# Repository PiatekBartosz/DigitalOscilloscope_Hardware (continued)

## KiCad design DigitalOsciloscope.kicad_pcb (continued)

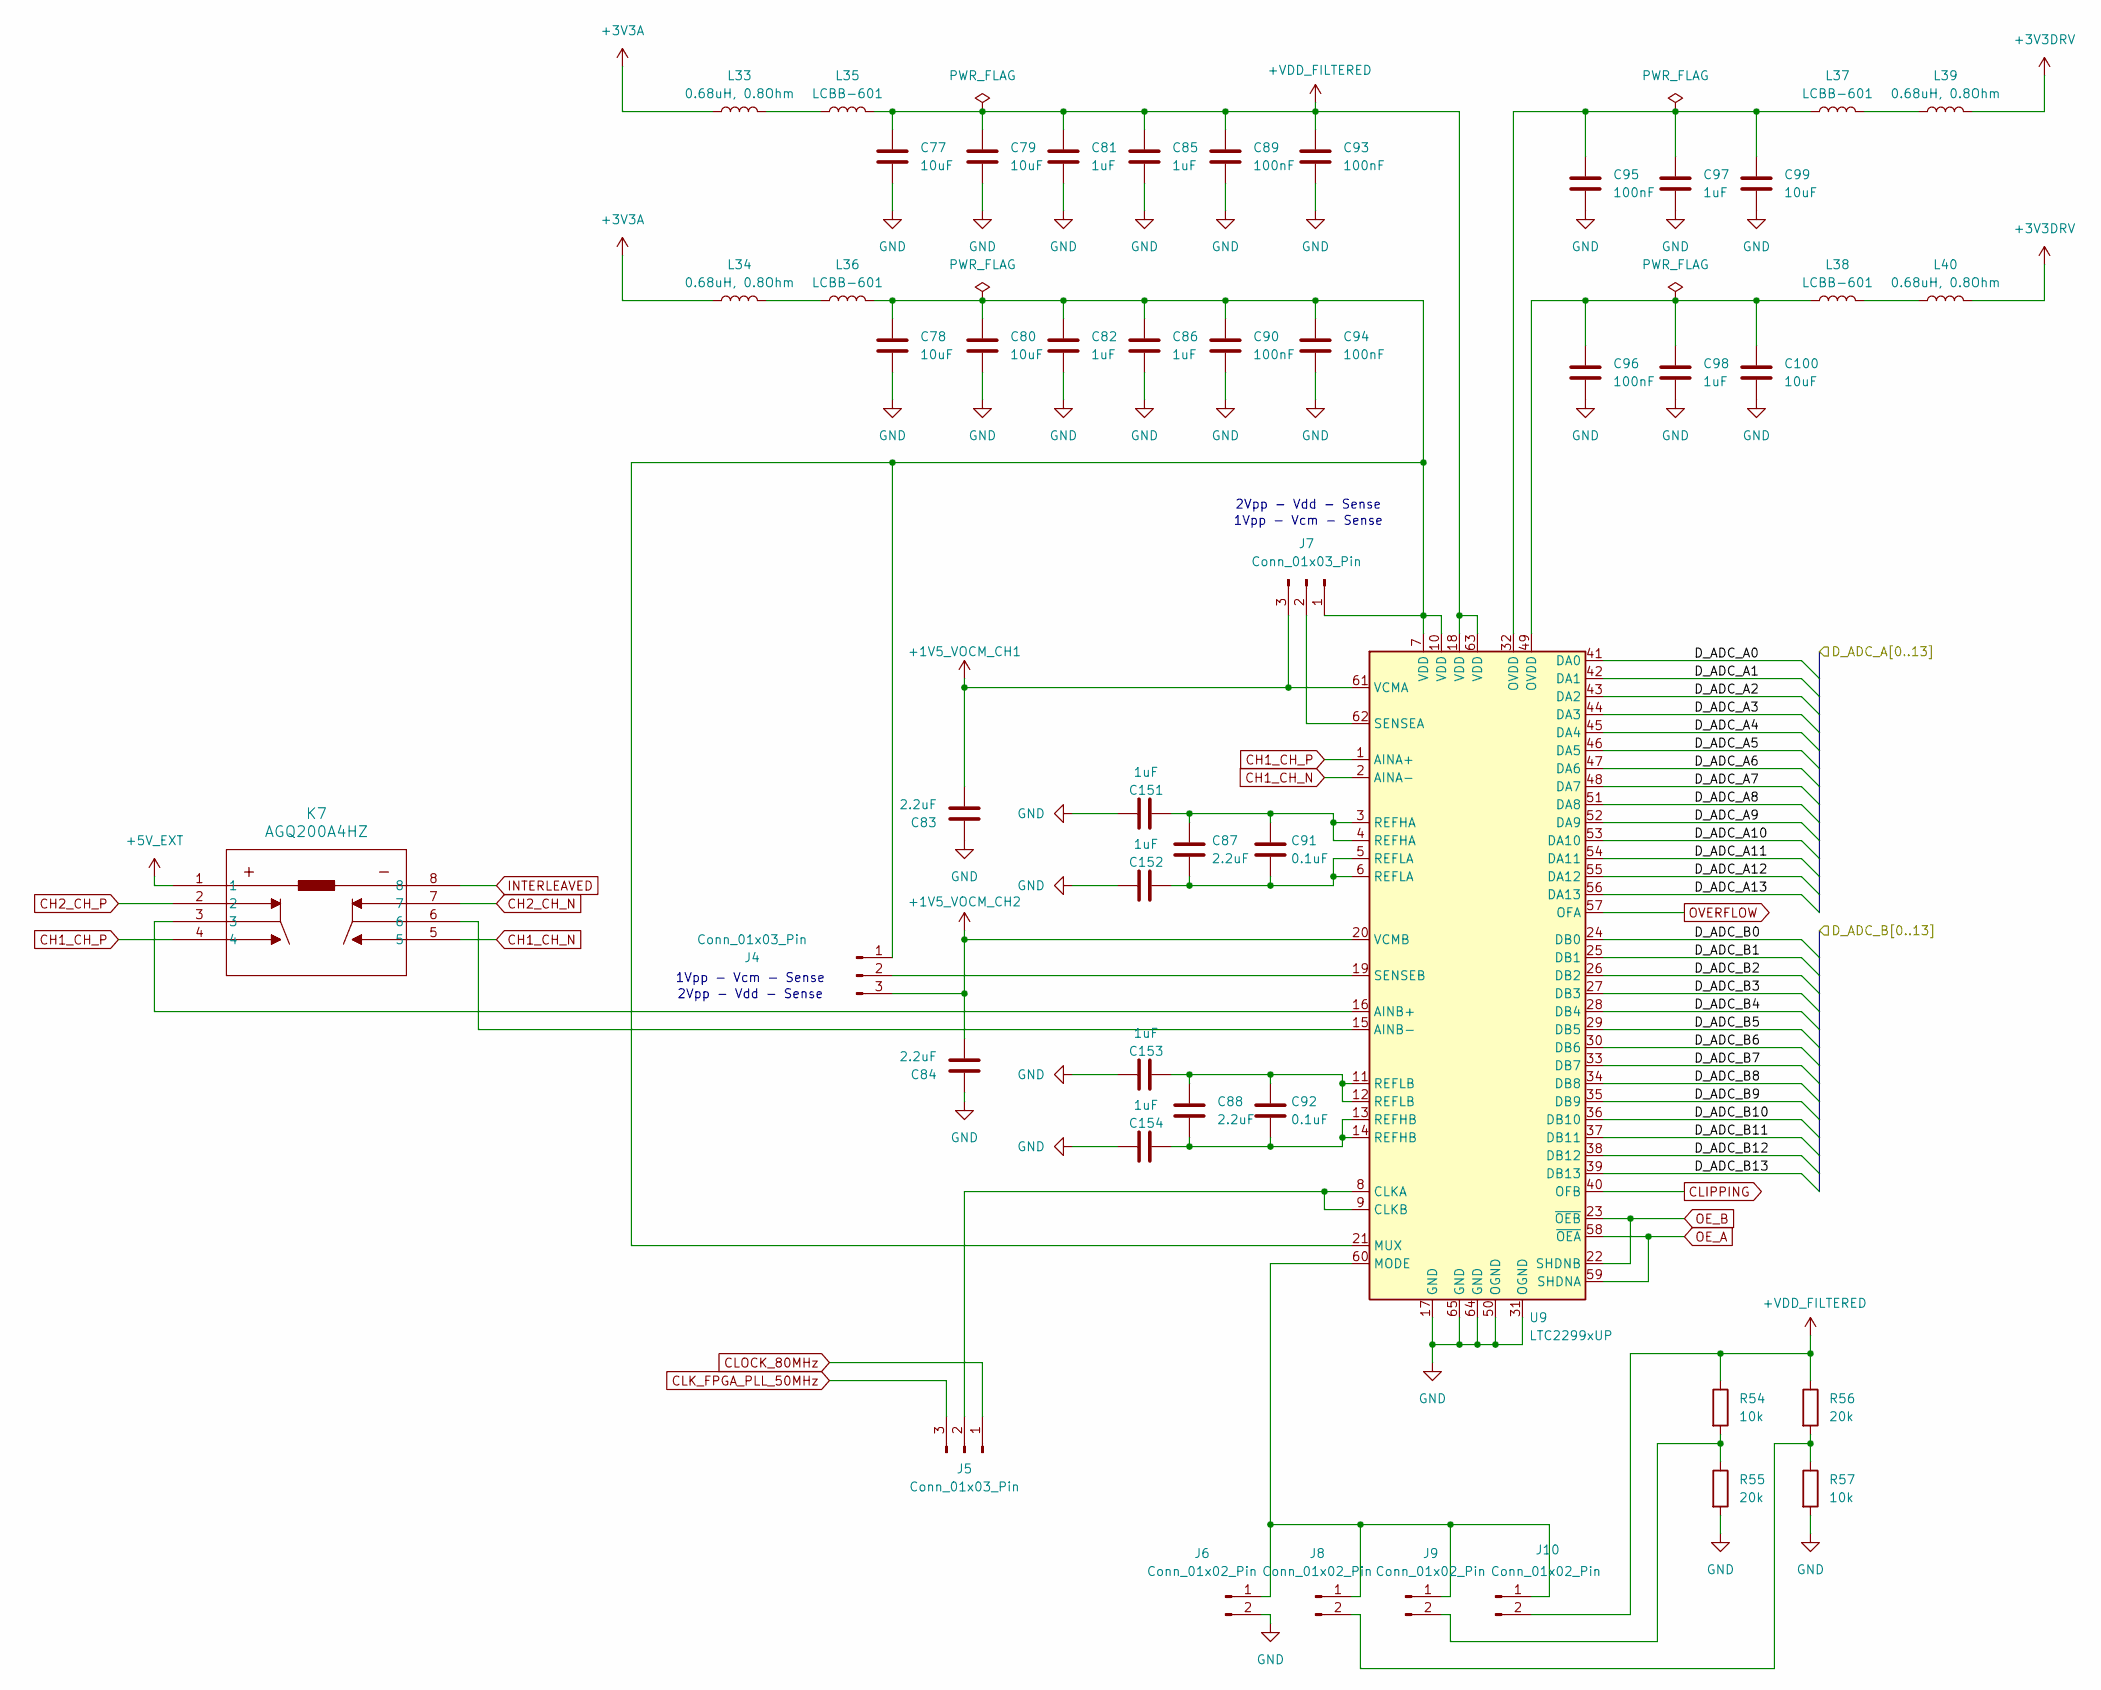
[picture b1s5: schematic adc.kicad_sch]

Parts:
C77, C78, C79, C80, C99, C100: 10uF; C_0805_2012Metric
C81, C82, C85, C86, C97, C98, C151, C152, C153, C154: 1uF; C_0805_2012Metric
C83, C84, C87, C88: 2.2uF; C_0805_2012Metric
C89, C90, C93, C94, C95, C96: 100nF; C_0805_2012Metric
C91, C92: 0.1uF; C_0805_2012Metric
J4, J5, J7: Conn_01x03_Pin; PinHeader_1x03_P2.54mm_Horizontal
J6, J8, J9, J10: Conn_01x02_Pin; PinHeader_1x02_P2.54mm_Horizontal
K7: AGQ200A4HZ; RELAY_AGQ_A_PAN
L33, L34, L39, L40: 0.68uH, 0.8Ohm; L_0805_2012Metric
L35, L36, L37, L38: LCBB-601; L_0805_2012Metric
R54, R57: 10k; R_0805_2012Metric
R55, R56: 20k; R_0805_2012Metric
U9: LTC2299xUP; QFN-64-1EP_9x9mm_P0.5mm_EP7.15x7.15mm

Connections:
+1V5_VOCM_CH1: C83.1, J7.3, U9.61 (VCMA); also elsewhere on the board
+1V5_VOCM_CH2: C84.1, J4.3, U9.20 (VCMB); also elsewhere on the board
+3V3A: L33.1, L34.1; also elsewhere on the board
+3V3DRV: L39.1, L40.1; also elsewhere on the board
+5V_EXT: K7.1; also elsewhere on the board
+VDD_FILTERED: C77.1, C79.1, C81.1, C85.1, C89.1, C93.1, J10.2, L35.2, R54.1, R56.1, U9.18 (VDD), U9.63 (VDD)
ADC_A_0: U9.41 (DA0); also elsewhere on the board
ADC_A_1: U9.42 (DA1); also elsewhere on the board
ADC_A_2: U9.43 (DA2); also elsewhere on the board
ADC_A_3: U9.44 (DA3); also elsewhere on the board
ADC_A_4: U9.45 (DA4); also elsewhere on the board
ADC_A_5: U9.46 (DA5); also elsewhere on the board
ADC_A_6: U9.47 (DA6); also elsewhere on the board
ADC_A_7: U9.48 (DA7); also elsewhere on the board
ADC_A_8: U9.51 (DA8); also elsewhere on the board
ADC_A_9: U9.52 (DA9); also elsewhere on the board
ADC_A_10: U9.53 (DA10); also elsewhere on the board
ADC_A_11: U9.54 (DA11); also elsewhere on the board
ADC_A_12: U9.55 (DA12); also elsewhere on the board
ADC_A_13: U9.56 (DA13); also elsewhere on the board
ADC_B_0: U9.24 (DB0); also elsewhere on the board
ADC_B_1: U9.25 (DB1); also elsewhere on the board
ADC_B_2: U9.26 (DB2); also elsewhere on the board
ADC_B_3: U9.27 (DB3); also elsewhere on the board
ADC_B_4: U9.28 (DB4); also elsewhere on the board
ADC_B_5: U9.29 (DB5); also elsewhere on the board
ADC_B_6: U9.30 (DB6); also elsewhere on the board
ADC_B_7: U9.33 (DB7); also elsewhere on the board
ADC_B_8: U9.34 (DB8); also elsewhere on the board
ADC_B_9: U9.35 (DB9); also elsewhere on the board
ADC_B_10: U9.36 (DB10); also elsewhere on the board
ADC_B_11: U9.37 (DB11); also elsewhere on the board
ADC_B_12: U9.38 (DB12); also elsewhere on the board
ADC_B_13: U9.39 (DB13); also elsewhere on the board
CH1_CH_N: K7.5, U9.2 (AINA-); also elsewhere on the board
CH1_CH_P: K7.4, U9.1 (AINA+); also elsewhere on the board
CH2_CH_N: K7.7; also elsewhere on the board
CH2_CH_P: K7.2; also elsewhere on the board
CLIPPING: U9.40 (OFB); also elsewhere on the board
CLK_FPGA_PLL_50MHz: J5.3; also elsewhere on the board
CLOCK_80MHz: J5.1; also elsewhere on the board
GND: C77.2, C78.2, C79.2, C80.2, C81.2, C82.2, C83.2, C84.2, C85.2, C86.2, C89.2, C90.2, C93.2, C94.2, C95.2, C96.2, C97.1, C98.1, C99.1, C100.1, C151.1, C152.1, C153.1, C154.1, J6.2, R55.2, R57.2, U9.17 (GND), U9.31 (OGND), U9.50 (OGND), U9.64 (GND), U9.65 (GND); also elsewhere on the board
INTERLEAVED: K7.8; also elsewhere on the board
unnamed: C95.1, C97.2, C99.2, L37.2, U9.32 (OVDD)
unnamed: C96.1, C98.2, C100.2, L38.2, U9.49 (OVDD)
unnamed: C87.1, C91.1, C151.2, U9.3 (REFHA), U9.4 (REFHA)
unnamed: C87.2, C91.2, C152.2, U9.5 (REFLA), U9.6 (REFLA)
unnamed: C88.1, C92.1, C153.2, U9.11 (REFLB), U9.12 (REFLB)
unnamed: C88.2, C92.2, C154.2, U9.13 (REFHB), U9.14 (REFHB)
unnamed: C78.1, C80.1, C82.1, C86.1, C90.1, C94.1, J4.1, J7.1, L36.2, U9.7 (VDD), U9.10 (VDD), U9.21 (MUX)
unnamed: J4.2, U9.19 (SENSEB)
unnamed: J5.2, U9.8 (CLKA), U9.9 (CLKB)
unnamed: J7.2, U9.62 (SENSEA)
unnamed: J8.2, R56.2, R57.1
unnamed: J9.2, R54.2, R55.1
unnamed: J6.1, J8.1, J9.1, J10.1, U9.60 (MODE)
unnamed: L33.2, L35.1
unnamed: L34.2, L36.1
unnamed: L37.1, L39.2
unnamed: L38.1, L40.2
unnamed: K7.3, U9.16 (AINB+)
unnamed: K7.6, U9.15 (AINB-)
OE_A: U9.58 (~OEA), U9.59 (SHDNA); also elsewhere on the board
OE_B: U9.22 (SHDNB), U9.23 (~OEB); also elsewhere on the board
OVERFLOW: U9.57 (OFA); also elsewhere on the board

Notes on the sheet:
2Vpp - Vdd - Sense
1Vpp - Vcm - Sense
